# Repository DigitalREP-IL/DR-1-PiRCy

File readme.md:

# PiRCy #

The Raspberry **Pi** **R**emote **C**ontrol Thing**y**

This is an extension board to add infrared remote control inputs and outputs to your Raspberry Pi.  

It is designed to replace your IR receiver, breadboard, and jumper wires with an elegantly positioned module.  This should increase the living-room acceptance factor of your Kodi-enabled Pi by at least 75%.

Along with the Vishay TSOP77438 IR Receiver, this extension has a VSBM2948 IR emitter to control other AV equipment, such as DVD players.  It has a half-angle (beam width) of 25 degrees, so alignment isn't too critical.

For the enterprising hacker, there are via pads for 3.3V, Ground, and GPIOs 4, 14, and 15.  

## Hardware Installation

Affix PiRCy to the 40-pin GPIO header as shown:

The IR components should face outward from the Pi, and ideally toward your couch.  PiRCy sits at the very end of the 40-pin GPIO header.

## Basic Software Configuration

The pin assignment of the IR receiver and IR emitter are on the defaults for the "lirc" kernel module on RPi models 0, A, and B.  You 
can test PiRCy by loading the kernel module and using the "mode2" command while pushing buttons on your remote.  At the terminal:

```
# sudo modprobe lirc_rpi
# mode2 -d /dev/lirc0
space 1192
pulse 601
space 1098
pulse 599
...
```

Press ```<CTRL-c> ``` to exit the mode2 program.  The ```irrecord``` utility is awesome for creating a new ```lircd.conf``` file if you have a remote that is not yet included in the database.  Launch it, then follow the instructions to record and assign your buttons.

## Media Center Distribution Configuration

Under OSMC, there is an option to enable lircd; it helpfully sets up the boot parameters in the background so a simple reboot 
after enabling is all it takes.  If you have a recognized remote, you are effectively finished now.  However, OSMC's configuration 
dialog lets you point at a custom configuration file as well, so you can use the ```lircd.conf``` that was created above by 
```irrecord```.

Due to some resource conflicts (interrupt latency primarily), the lirc kernel module is considered somewhat deprecated for media 
center use.  Kodi and LibreElec recognize the built-in ```gpio-ir``` module natively.

Within the config.txt file in /boot, add the following parameter (no ```gpio_pin``` options needed):

```dtparam=gpio-ir```

Reboot your Raspberry Pi to effect the change to the boot options.

To test, run the keytable test utility from a terminal:

``` # ir-keytable -t ```

Push some buttons on your remote to see if the keytable test returns mark/space data.

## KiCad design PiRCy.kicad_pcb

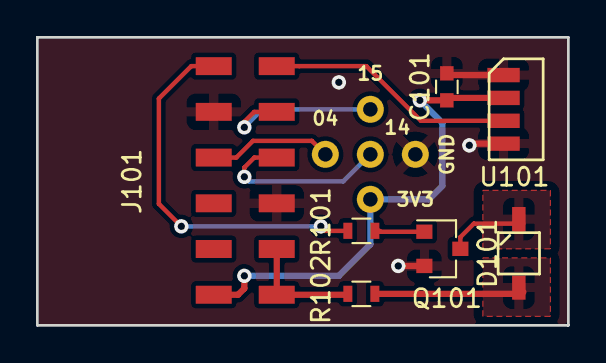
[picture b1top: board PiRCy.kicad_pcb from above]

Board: 2 copper layers, 29.5 x 16.0 mm, 12 parts (0 on the bottom side), 11 nets.

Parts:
3V3: 3V3; Measurement_Point_Round-TH_Small
04: GPIO04; Measurement_Point_Round-TH_Small
14: GPIO14; Measurement_Point_Round-TH_Small
15: GPIO15; Measurement_Point_Round-TH_Small
C101: 1uF; C_0603
D101: VSMB2948; VSMG28011G
GND: GND; Measurement_Point_Round-TH_Small
J101: Conn_02x06_Odd_Even; Harwin-M20-02x06_RA
Q101: 2N7002; SOT-23
R101: 560; R_0603
R102: 56; R_0603
U101: TSOP77438; Heim

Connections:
+3V3: 3V3.1, C101.1, J101.1, U101.2
+5V: J101.2, J101.4, R102.1
GND: C101.2, GND.1, J101.6, J101.9, Q101.2, U101.1, U101.4
GPIO04: 04.1, J101.7
GPIO14: 14.1, J101.8
GPIO15: 15.1, J101.10
GPIO17: J101.11, R101.2
GPIO18: J101.12, U101.3
unnamed: D101.1, Q101.3
unnamed: D101.2, R102.2
unnamed: Q101.1, R101.1
